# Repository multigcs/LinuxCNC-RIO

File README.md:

# LinuxCNC-RIO

please use: https://github.com/multigcs/riocore

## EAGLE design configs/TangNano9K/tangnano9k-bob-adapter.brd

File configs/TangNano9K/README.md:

# Tang Nano 9K with 5axis-BOB

https://wiki.sipeed.com/hardware/en/tang/Tang-Nano-9K/Nano-9K.html

Install: see INSTALL.md

## Known-Issues:
* openFPGAloader will not work on Raspberry Pi, you have to use another host to flash the FPGA !
* sometimes i have problems with the opensource toolchain and extended configurations, like encoder value will not change
* you can also using the gowin toolchain if you have problems with the opensource one, all required files are generated

### LinuxCNC-RIO mixed joint types (on TangNano9K - FPGA)
")

## BOB-Adapter SPI-Pins:

| BOB-Adapter | FUNC | FPGA-Pin |Raspberry-GPIO | Raspberry-Pin |
| --- | --- | --- | --- | --- |
| 1 | 5V |  |  | 2 |
| 2 | MOSI | 48 | GPIO10 (MOSI) | 19 |
| 3 | MISO |  49 |GPIO9 (MISO) | 21 |
| 4 | SCK |  31 |GPIO11 (SCLK) | 23 |
| 5 | CS |  32 |GPIO7 (CE1) | 26 |
| 6 | GND | | | 6 |

## BOB-Adapter Expansion-Pins:
| BOB-Adapter | FUNC | FPGA-Pin | 
| --- | --- | --- |
| 1 | OUT | 73 |
| 2 | IN | 72 |
| 3 | CLK | 71 |
| 4 | LOAD | 70 |
| 5 | 5V | |
| 6 | GND | |

## BOB-Adapter extra Input-Pins:
| BOB-Adapter | FUNC | FPGA-Pin |
| --- | --- | --- |
| 1 | 5V | |
| 2 | DIN5 | 79 |
| 3 | DIN6 | 80 |
| 4 | DIN7 | 81 |
| 5 | DIN8 | 82 |
| 6 | DIN9 | 83 |
| 7 | DIN10 | 84 |
| 8 | DIN11 | 85 |
| 9 | DIN12 | 86 |
| 10 | GND | |

## Mapping: 5Axis-BOB to FPGA 

| BOB5X | FUNC | FPGA-Pin |
| --- | --- | --- |
| P1 | PWM | 55 |
| P2 | STP_X | 54 |
| P3 | DIR_X | 53 |
| P4 | STP_Y | 51 |
| P5 | DIR_Y | 42 |
| P6 | STP_Z | 41 |
| P7 | DIR_Z | 35 |
| P8 | STP_A | 40 |
| P9 | DIR_A | 34 |
| P10 | DIN0 | 33 |
| P11 | DIN1 | 30 |
| P12 | DIN2 | 29 |
| P13 | DIN3 | 28 |
| P14 | EN | 69 |
| P15 | DIN4 | 68 |
| P16 | STP_B | 57 |
| P17 | DIR_B / Relais | 56 |

## Mapping: FPGA Onboard Components

| Component | FUNC | FPGA-Pin |
| --- | --- | --- |
| LED1 | BLINK | 10 |
| LED2 | ERROR | 11 |
| LED3 | DOUT1 | 13 |
| LED4 | DOUT2 | 14 |
| LED5 | DOUT3 | 15 |
| LED6 | DOUT4 | 16 |
| BTN_S1 | VIN1+ | 4 |
| BTN_S2 | VIN1- | 3 |

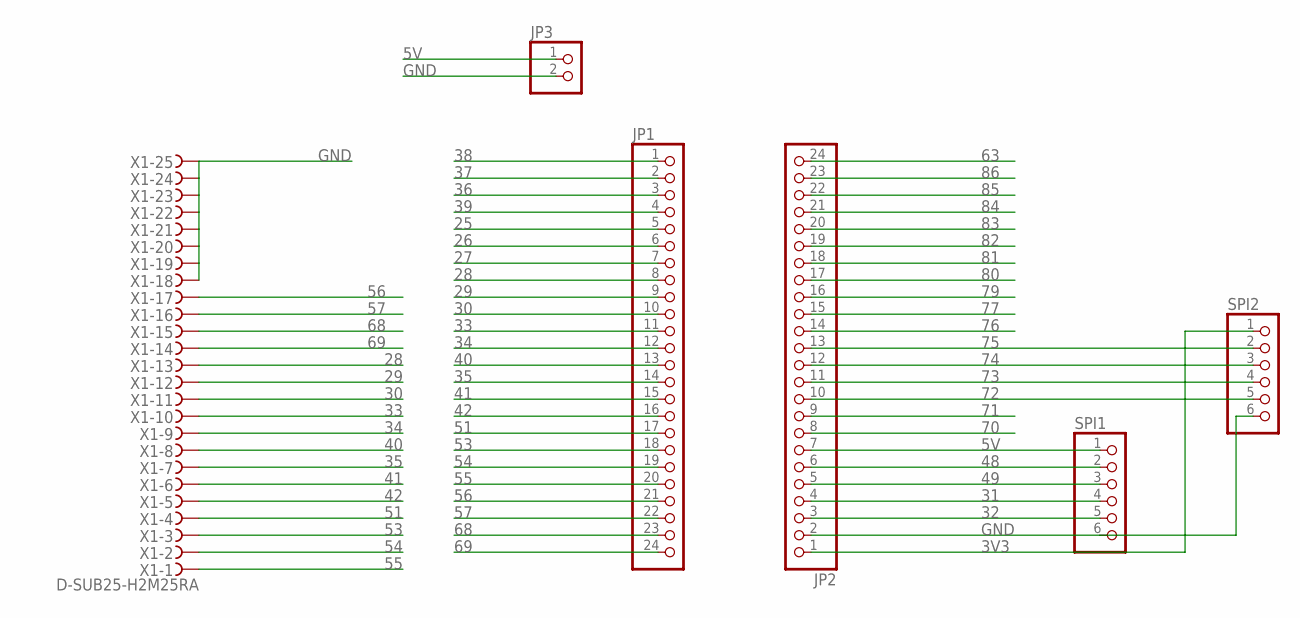
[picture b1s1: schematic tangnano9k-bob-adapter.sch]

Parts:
JP1, JP2: PINHD-1X24; 1X24
JP3: PINHD-1X2; 1X02
SPI1, SPI2: PINHD-1X6; 1X06
X1: D-SUB25-H2M25RA; H2M25RA

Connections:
3V3: JP2.1, SPI2.1
5V: JP2.7, JP3.1, SPI1.1
25: JP1.5
26: JP1.6
27: JP1.7
28: JP1.8, X1.13
29: JP1.9, X1.12
30: JP1.10, X1.11
31: JP2.4, SPI1.4
32: JP2.3, SPI1.5
33: JP1.11, X1.10
34: JP1.12, X1.9
35: JP1.14, X1.7
36: JP1.3
37: JP1.2
38: JP1.1
39: JP1.4
40: JP1.13, X1.8
41: JP1.15, X1.6
42: JP1.16, X1.5
48: JP2.6, SPI1.2
49: JP2.5, SPI1.3
51: JP1.17, X1.4
53: JP1.18, X1.3
54: JP1.19, X1.2
55: JP1.20, X1.1
56: JP1.21, X1.17
57: JP1.22, X1.16
63: JP2.24
68: JP1.23, X1.15
69: JP1.24, X1.14
70: JP2.8
71: JP2.9
72: JP2.10, SPI2.5
73: JP2.11, SPI2.4
74: JP2.12, SPI2.3
75: JP2.13, SPI2.2
76: JP2.14
77: JP2.15
79: JP2.16
80: JP2.17
81: JP2.18
82: JP2.19
83: JP2.20
84: JP2.21
85: JP2.22
86: JP2.23
GND: JP2.2, JP3.2, SPI1.6, SPI2.6, X1.18, X1.19, X1.20, X1.21, X1.22, X1.23, X1.24, X1.25

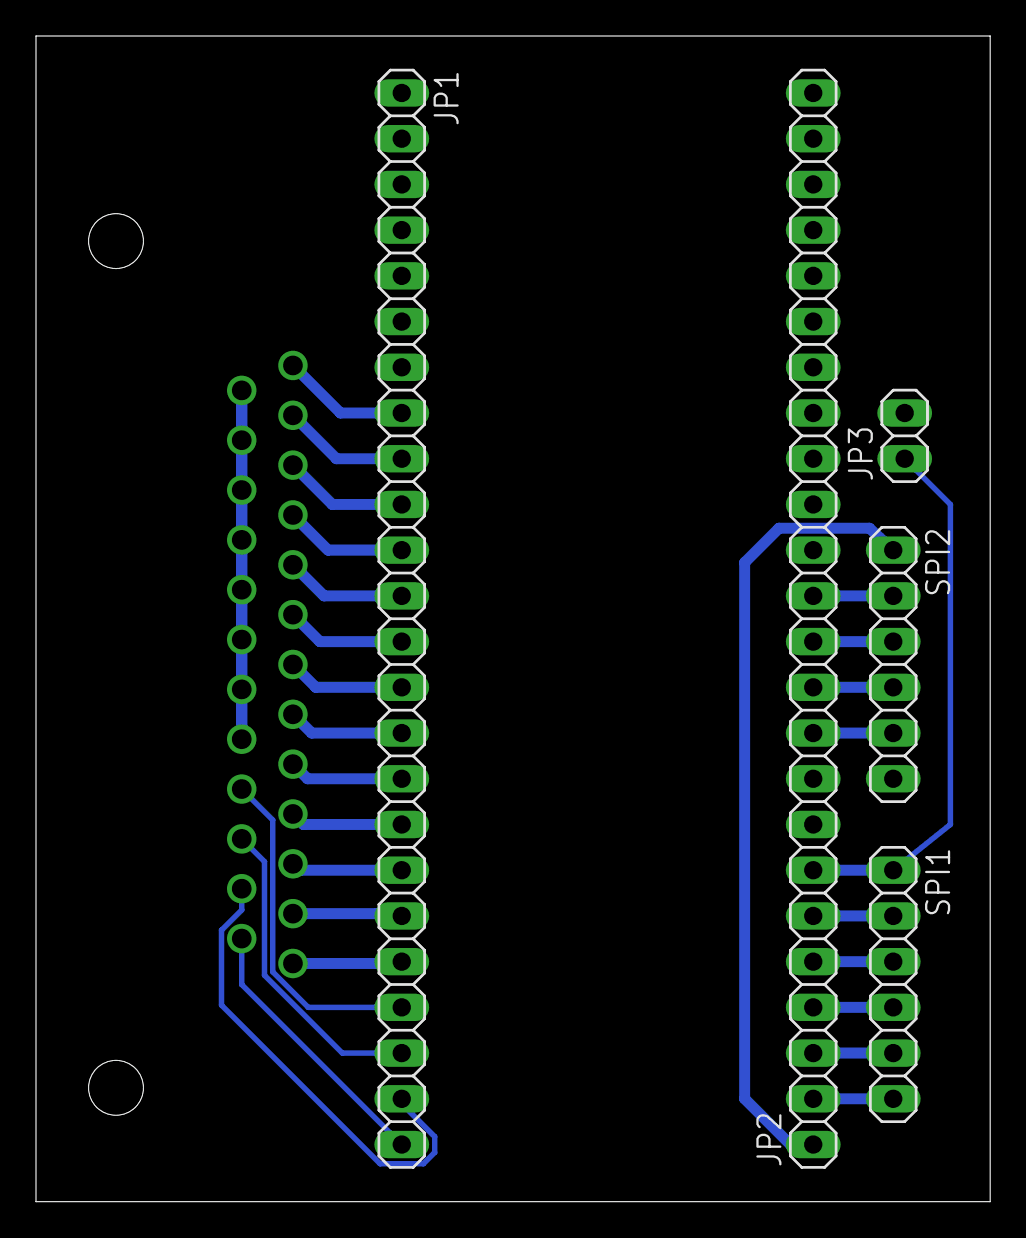
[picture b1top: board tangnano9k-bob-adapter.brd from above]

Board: 2 copper layers, 53.0 x 64.8 mm, 6 parts (1 on the bottom side), 28 nets.

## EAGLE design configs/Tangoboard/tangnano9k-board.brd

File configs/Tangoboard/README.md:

# Tango-Board for Tang Nano 9K

https://wiki.sipeed.com/hardware/en/tang/Tang-Nano-9K/Nano-9K.html

Install: see INSTALL.md

## Known-Issues:
* openFPGAloader will not work on Raspberry Pi, you have to use another host to flash the FPGA !
* sometimes i have problems with the opensource toolchain and extended configurations, like encoder value will not change
* you can also using the gowin toolchain if you have problems with the opensource one, all required files are generated

## BOM:

[Reichelt](https://www.reichelt.de/my/2063538)

## Pinout:

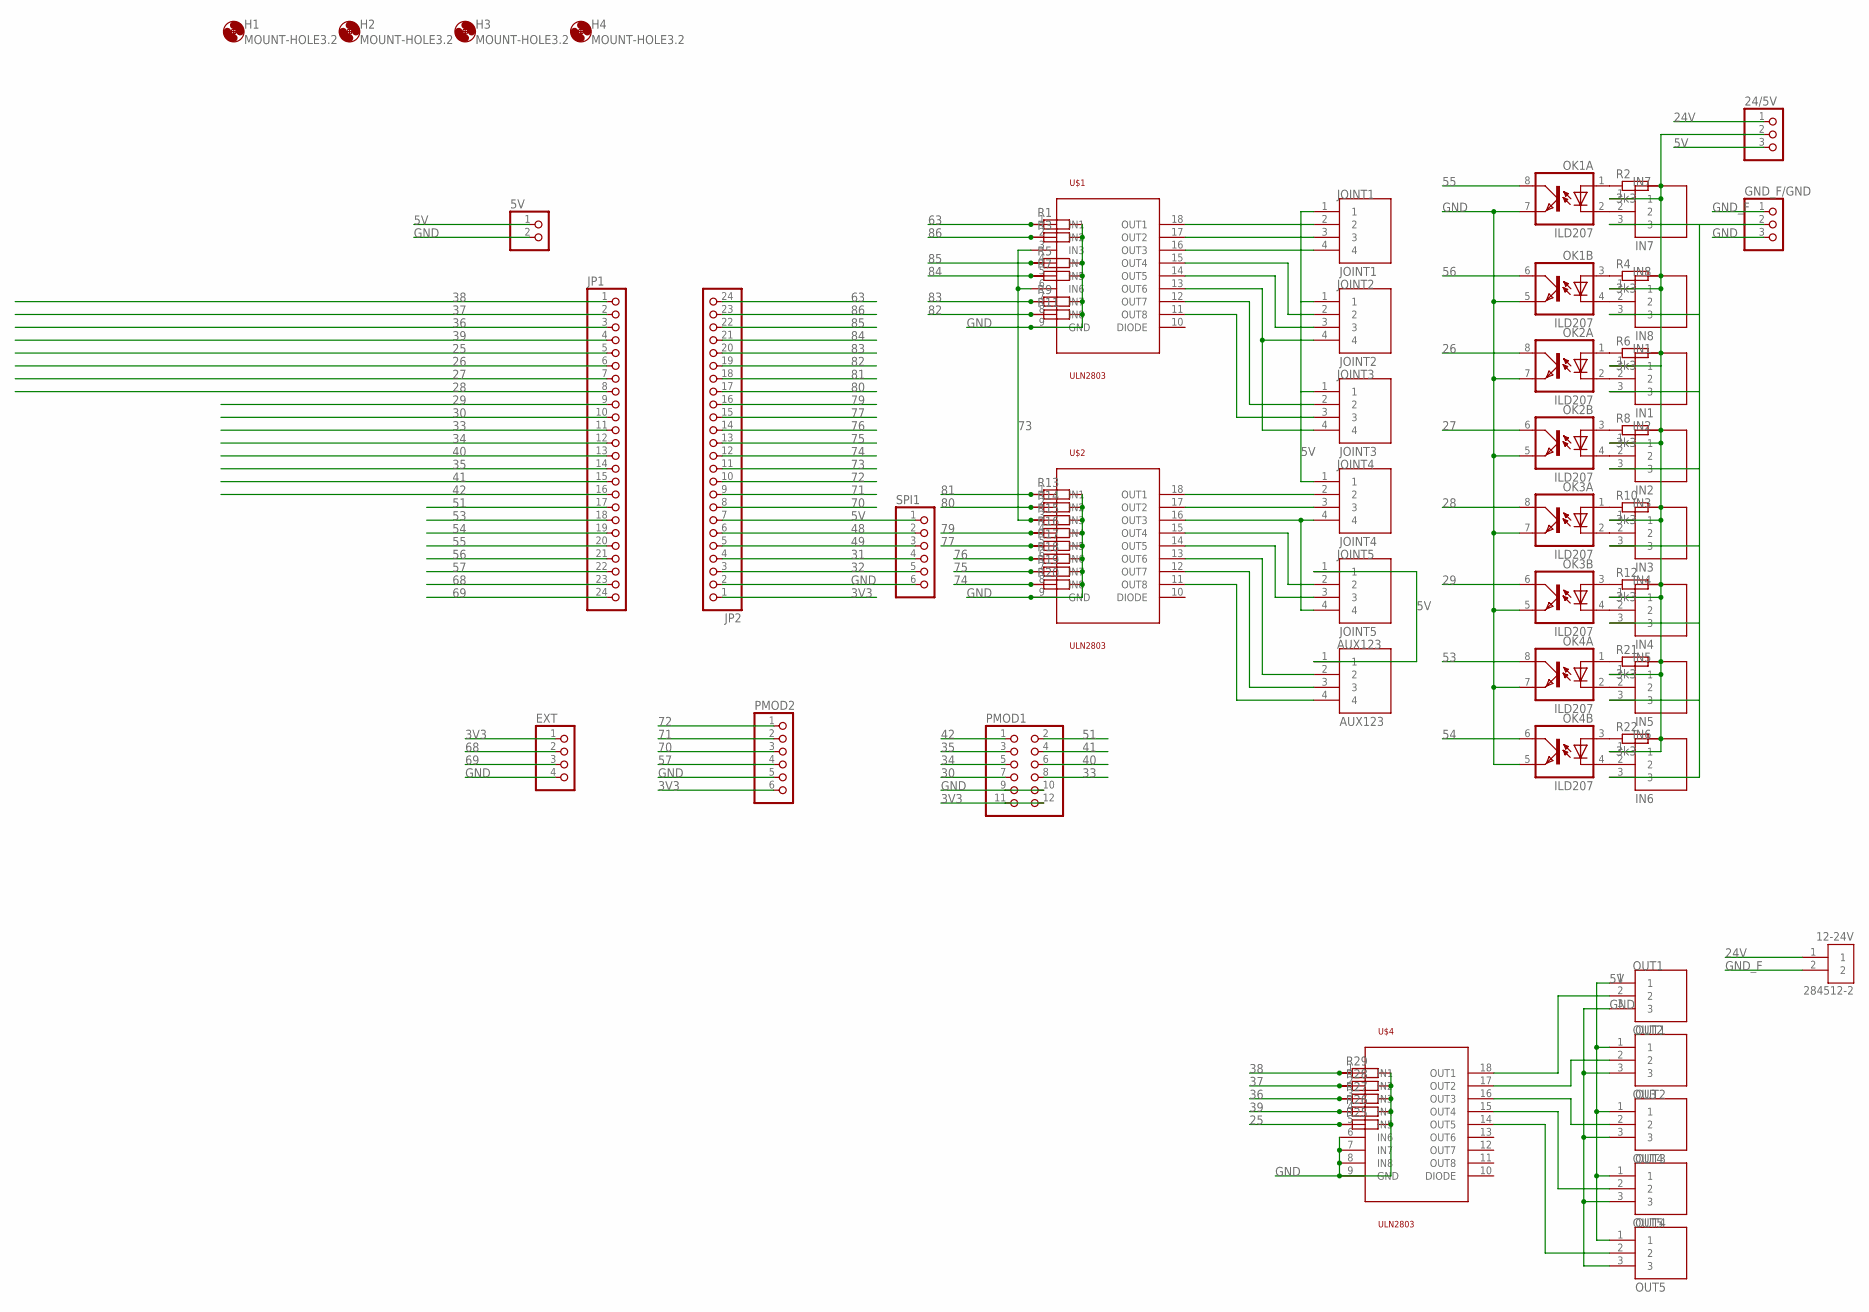
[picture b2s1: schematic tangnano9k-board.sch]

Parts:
5V: PINHD-1X2; 1X02
12-24V: 284512-2; TE_284512-2
24/5V: PINHD-1X3; 1X03
AUX123: AUX123; TE_284512-4
EXT: PINHD-1X4; 1X04
GND_F/GND: PINHD-1X3; 1X03
H1, H2, H3, H4: MOUNT-HOLE3.2; 3,2
IN1: IN1; TE_284512-3
IN2: IN2; TE_284512-3
IN3: IN3; TE_284512-3
IN4: IN4; TE_284512-3
IN5: IN5; TE_284512-3
IN6: IN6; TE_284512-3
IN7: IN7; TE_284512-3
IN8: IN8; TE_284512-3
JOINT1: JOINT1; TE_284512-4
JOINT2: JOINT2; TE_284512-4
JOINT3: JOINT3; TE_284512-4
JOINT4: JOINT4; TE_284512-4
JOINT5: JOINT5; TE_284512-4
JP1, JP2: PINHD-1X24; 1X24
OK1, OK2, OK3, OK4: ILD207; SOIC08
OU3: OUT3; TE_284512-3
OUT1: OUT1; TE_284512-3
OUT2: OUT2; TE_284512-3
OUT4: OUT4; TE_284512-3
OUT5: OUT5; TE_284512-3
PMOD1: PINHD-2X6; 2X06
PMOD2: PINHD-1X6; 1X06
R1, R3, R5, R7, R9, R11, R13, R14, R15, R16, R17, R18, R19, R20, R25, R26, R27, R28, R29: R-EU_M0805; M0805
R2, R4, R6, R8, R10, R12, R21, R22: 3k3; M0805
SPI1: PINHD-1X6; 1X06
U$1, U$2, U$4: ULN2803; SO18L

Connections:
3V3: EXT.1, JP2.1, PMOD1.11, PMOD1.12, PMOD2.6
5V: 5V.1, 24/5V.3, AUX123.1, JOINT1.1, JOINT2.1, JOINT3.1, JOINT4.1, JOINT5.1, JP2.7, OU3.1, OUT1.1, OUT2.1, OUT4.1, OUT5.1, SPI1.1
24V: 12-24V.1, 24/5V.1
25: JP1.5, R25.1, U$4.5 (IN5)
26: JP1.6, OK2.8 (COL)
27: JP1.7, OK2.6 (COL)
28: JP1.8, OK3.8 (COL)
29: JP1.9, OK3.6 (COL)
30: JP1.10, PMOD1.7
31: JP2.4, SPI1.4
32: JP2.3, SPI1.5
33: JP1.11, PMOD1.8
34: JP1.12, PMOD1.5
35: JP1.14, PMOD1.3
36: JP1.3, R27.1, U$4.3 (IN3)
37: JP1.2, R28.1, U$4.2 (IN2)
38: JP1.1, R29.1, U$4.1 (IN1)
39: JP1.4, R26.1, U$4.4 (IN4)
40: JP1.13, PMOD1.6
41: JP1.15, PMOD1.4
42: JP1.16, PMOD1.1
48: JP2.6, SPI1.2
49: JP2.5, SPI1.3
51: JP1.17, PMOD1.2
53: JP1.18, OK4.8 (COL)
54: JP1.19, OK4.6 (COL)
55: JP1.20, OK1.8 (COL)
56: JP1.21, OK1.6 (COL)
57: JP1.22, PMOD2.4
63: JP2.24, R1.1, U$1.1 (IN1)
68: EXT.2, JP1.23
69: EXT.3, JP1.24
70: JP2.8, PMOD2.3
71: JP2.9, PMOD2.2
72: JP2.10, PMOD2.1
73: JP2.11, R15.1, U$1.3 (IN3), U$1.6 (IN6), U$2.3 (IN3)
74: JP2.12, R20.1, U$2.8 (IN8)
75: JP2.13, R19.1, U$2.7 (IN7)
76: JP2.14, R18.1, U$2.6 (IN6)
77: JP2.15, R17.1, U$2.5 (IN5)
79: JP2.16, R16.1, U$2.4 (IN4)
80: JP2.17, R14.1, U$2.2 (IN2)
81: JP2.18, R13.1, U$2.1 (IN1)
82: JP2.19, R11.1, U$1.8 (IN8)
83: JP2.20, R9.1, U$1.7 (IN7)
84: JP2.21, R7.1, U$1.5 (IN5)
85: JP2.22, R5.1, U$1.4 (IN4)
86: JP2.23, R3.1, U$1.2 (IN2)
GND: 5V.2, EXT.4, GND_F/GND.3, JP2.2, OK1.5 (EMIT), OK1.7 (EMIT), OK2.5 (EMIT), OK2.7 (EMIT), OK3.5 (EMIT), OK3.7 (EMIT), OK4.5 (EMIT), OK4.7 (EMIT), OU3.3, OUT1.3, OUT2.3, OUT4.3, OUT5.3, PMOD1.9, PMOD1.10, PMOD2.5, R1.2, R3.2, R5.2, R7.2, R9.2, R11.2, R13.2, R14.2, R15.2, R16.2, R17.2, R18.2, R19.2, R20.2, R25.2, R26.2, R27.2, R28.2, R29.2, SPI1.6, U$1.9 (GND), U$2.9 (GND), U$4.6 (IN6), U$4.7 (IN7), U$4.8 (IN8), U$4.9 (GND)
GND_F: 12-24V.2, GND_F/GND.1
unnamed: JOINT1.4, U$1.16 (OUT3)
unnamed: JOINT1.3, U$1.17 (OUT2)
unnamed: JOINT1.2, U$1.18 (OUT1)
unnamed: JOINT2.2, U$1.15 (OUT4)
unnamed: JOINT2.3, U$1.14 (OUT5)
unnamed: JOINT2.4, JOINT3.4, U$1.13 (OUT6)
unnamed: JOINT3.2, U$1.12 (OUT7)
unnamed: JOINT3.3, U$1.11 (OUT8)
unnamed: JOINT4.2, U$2.18 (OUT1)
unnamed: JOINT4.3, U$2.17 (OUT2)
unnamed: JOINT4.4, JOINT5.4, U$2.16 (OUT3)
unnamed: JOINT5.2, U$2.15 (OUT4)
unnamed: JOINT5.3, U$2.14 (OUT5)
unnamed: AUX123.2, U$2.13 (OUT6)
unnamed: AUX123.3, U$2.12 (OUT7)
unnamed: AUX123.4, U$2.11 (OUT8)
unnamed: IN7.2, OK1.2 (C)
unnamed: IN8.2, OK1.4 (C)
unnamed: IN1.2, OK2.2 (C)
unnamed: IN2.2, OK2.4 (C)
unnamed: IN3.2, OK3.2 (C)
unnamed: IN4.2, OK3.4 (C)
unnamed: IN5.2, OK4.2 (C)
unnamed: IN6.2, OK4.4 (C)
unnamed: OK1.1 (A), R2.1
unnamed: OK1.3 (A), R4.1
unnamed: OK2.1 (A), R6.1
unnamed: OK2.3 (A), R8.1
unnamed: OK3.1 (A), R10.1
unnamed: OK3.3 (A), R12.1
unnamed: OK4.1 (A), R21.1
unnamed: OK4.3 (A), R22.1
unnamed: OUT2.2, U$4.17 (OUT2)
unnamed: OU3.2, U$4.16 (OUT3)
unnamed: OUT4.2, U$4.15 (OUT4)
unnamed: OUT5.2, U$4.14 (OUT5)
unnamed: OUT1.2, U$4.18 (OUT1)
unnamed: 24/5V.2, IN1.1, IN2.1, IN3.1, IN4.1, IN5.1, IN6.1, IN7.1, IN8.1, R2.2, R4.2, R6.2, R8.2, R10.2, R12.2, R21.2, R22.2
unnamed: GND_F/GND.2, IN1.3, IN2.3, IN3.3, IN4.3, IN5.3, IN6.3, IN7.3, IN8.3

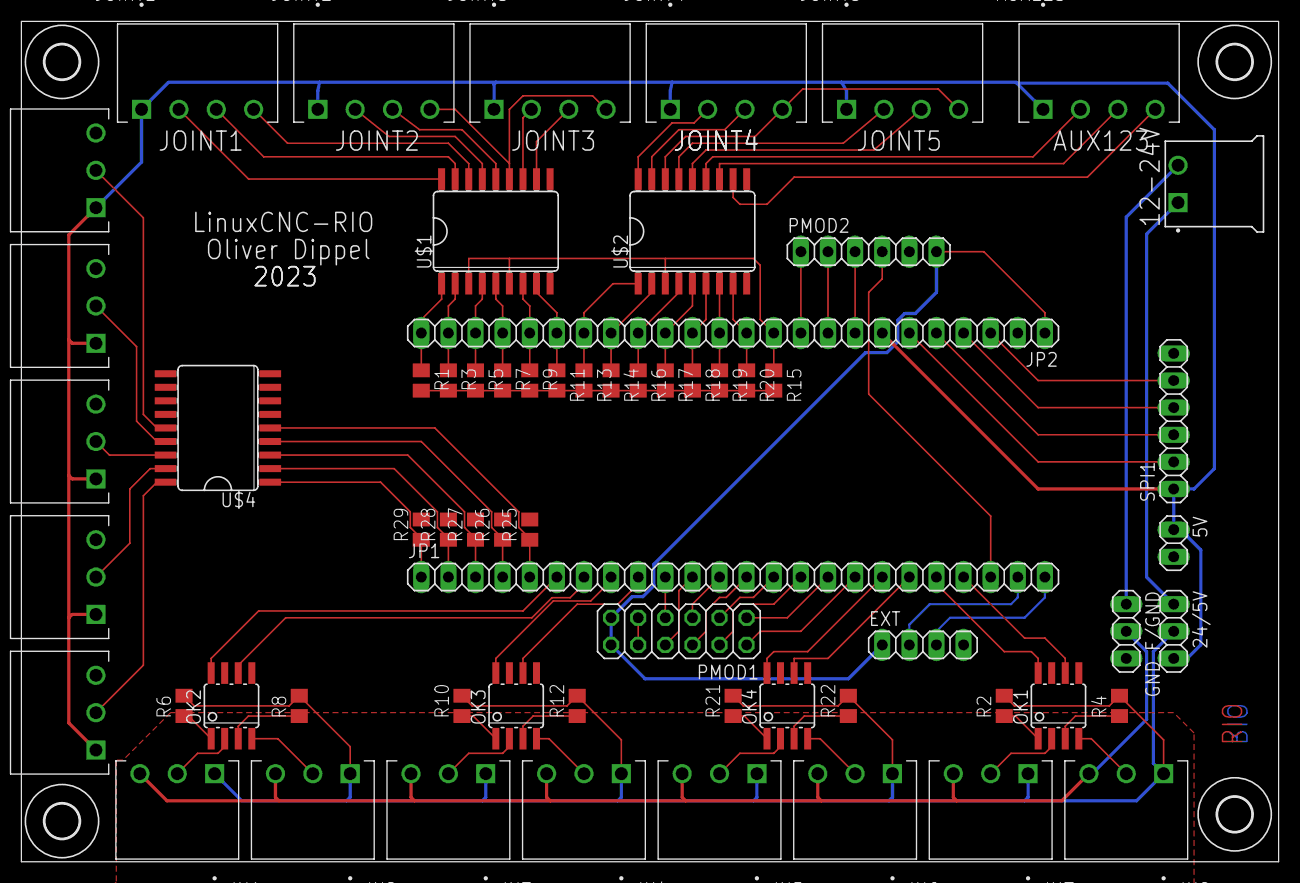
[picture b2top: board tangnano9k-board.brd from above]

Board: 2 copper layers, 117.8 x 78.7 mm, 67 parts (0 on the bottom side), 89 nets.

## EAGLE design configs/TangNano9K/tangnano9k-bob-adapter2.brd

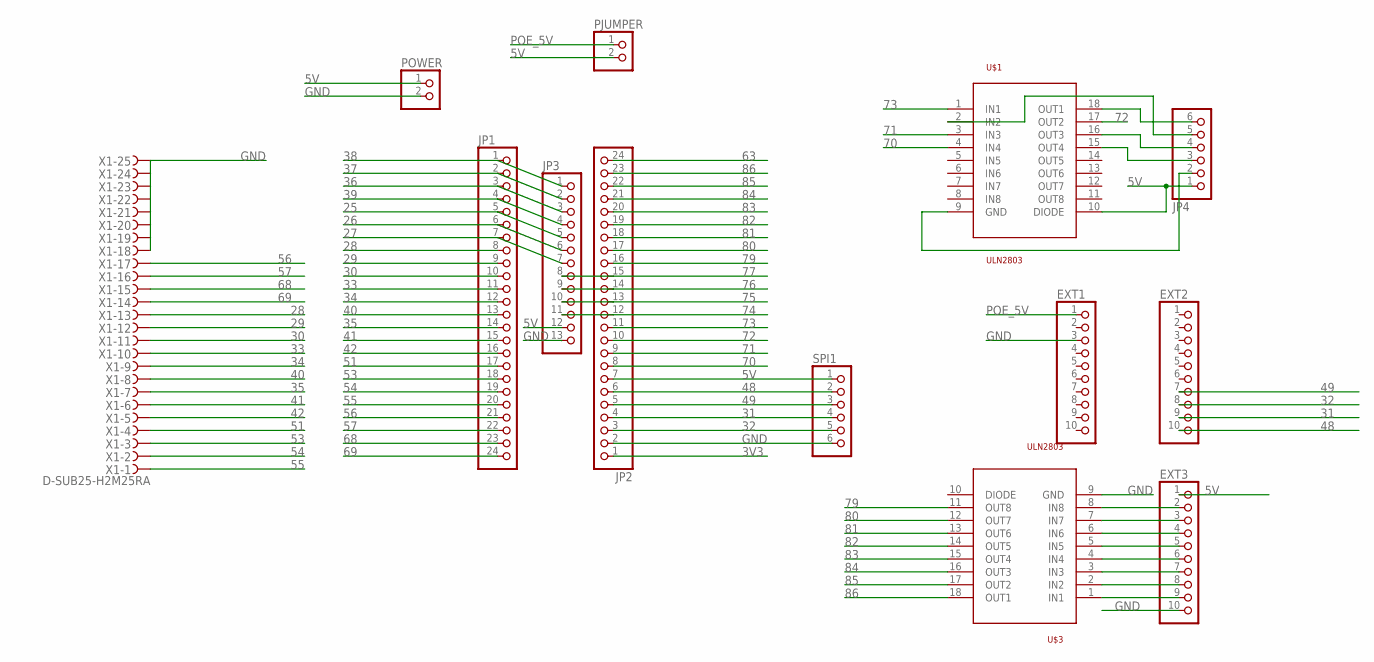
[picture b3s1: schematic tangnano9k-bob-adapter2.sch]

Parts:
EXT1, EXT2, EXT3: PINHD-1X10; 1X10
JP1, JP2: PINHD-1X24; 1X24
JP3: PINHD-1X13; 1X13
JP4: PINHD-1X6/90; 1X06/90
PJUMPER: PINHD-1X2; 1X02
POWER: PINHD-1X2; 1X02
SPI1: PINHD-1X6; 1X06
U$1, U$3: ULN2803; SO18L
X1: D-SUB25-H2M25RA; H2M25RA

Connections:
3V3: JP2.1
5V: EXT3.1, JP2.7, JP3.12, JP4.1, PJUMPER.2, POWER.1, SPI1.1, U$1.10 (DIODE)
25: JP1.5, JP3.5
26: JP1.6, JP3.6
27: JP1.7, JP3.7
28: JP1.8, X1.13
29: JP1.9, X1.12
30: JP1.10, X1.11
31: EXT2.9, JP2.4, SPI1.4
32: EXT2.8, JP2.3, SPI1.5
33: JP1.11, X1.10
34: JP1.12, X1.9
35: JP1.14, X1.7
36: JP1.3, JP3.3
37: JP1.2, JP3.2
38: JP1.1, JP3.1
39: JP1.4, JP3.4
40: JP1.13, X1.8
41: JP1.15, X1.6
42: JP1.16, X1.5
48: EXT2.10, JP2.6, SPI1.2
49: EXT2.7, JP2.5, SPI1.3
51: JP1.17, X1.4
53: JP1.18, X1.3
54: JP1.19, X1.2
55: JP1.20, X1.1
56: JP1.21, X1.17
57: JP1.22, X1.16
63: JP2.24
68: JP1.23, X1.15
69: JP1.24, X1.14
70: JP2.8, U$1.4 (IN4)
71: JP2.9, U$1.3 (IN3)
72: JP2.10, U$1.17 (OUT2)
73: JP2.11, U$1.1 (IN1)
74: JP2.12, JP3.11
75: JP2.13, JP3.10
76: JP2.14, JP3.9
77: JP2.15, JP3.8
79: JP2.16, U$3.11 (OUT8)
80: JP2.17, U$3.12 (OUT7)
81: JP2.18, U$3.13 (OUT6)
82: JP2.19, U$3.14 (OUT5)
83: JP2.20, U$3.15 (OUT4)
84: JP2.21, U$3.16 (OUT3)
85: JP2.22, U$3.17 (OUT2)
86: JP2.23, U$3.18 (OUT1)
GND: EXT1.3, EXT3.10, JP2.2, JP3.13, JP4.2, POWER.2, SPI1.6, U$1.9 (GND), U$3.9 (GND), X1.18, X1.19, X1.20, X1.21, X1.22, X1.23, X1.24, X1.25
unnamed: EXT3.9, U$3.1 (IN1)
unnamed: JP4.6, U$1.18 (OUT1)
unnamed: JP4.5, U$1.2 (IN2)
unnamed: JP4.4, U$1.16 (OUT3)
unnamed: JP4.3, U$1.15 (OUT4)
unnamed: EXT3.8, U$3.2 (IN2)
unnamed: EXT3.7, U$3.3 (IN3)
unnamed: EXT3.6, U$3.4 (IN4)
unnamed: EXT3.5, U$3.5 (IN5)
unnamed: EXT3.4, U$3.6 (IN6)
unnamed: EXT3.3, U$3.7 (IN7)
unnamed: EXT3.2, U$3.8 (IN8)
POE_5V: EXT1.1, PJUMPER.1

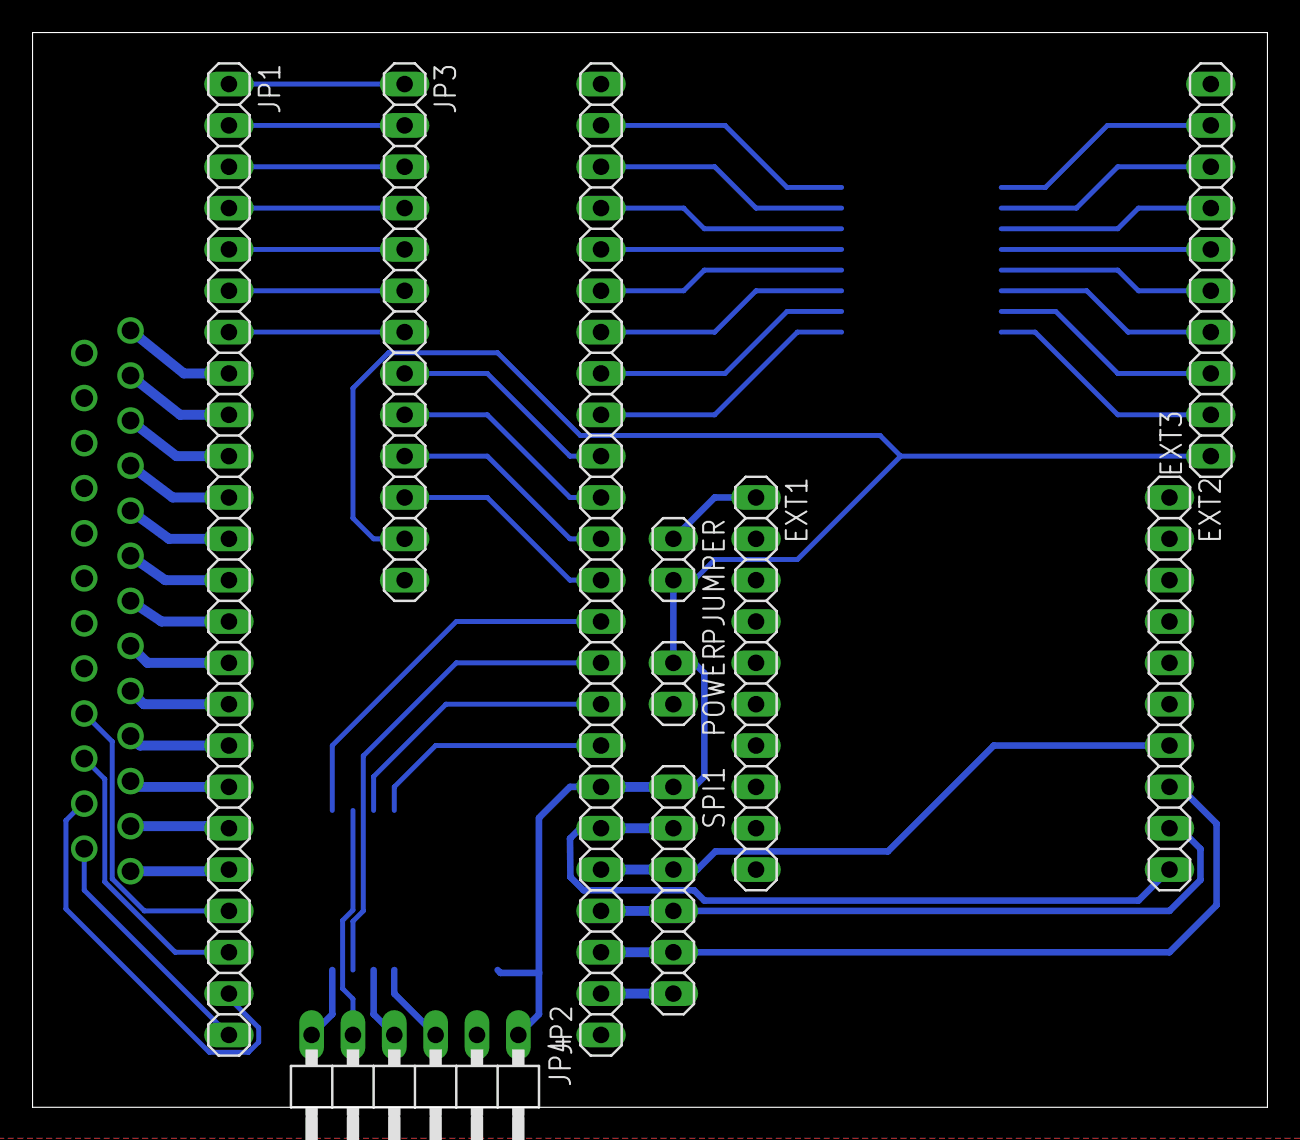
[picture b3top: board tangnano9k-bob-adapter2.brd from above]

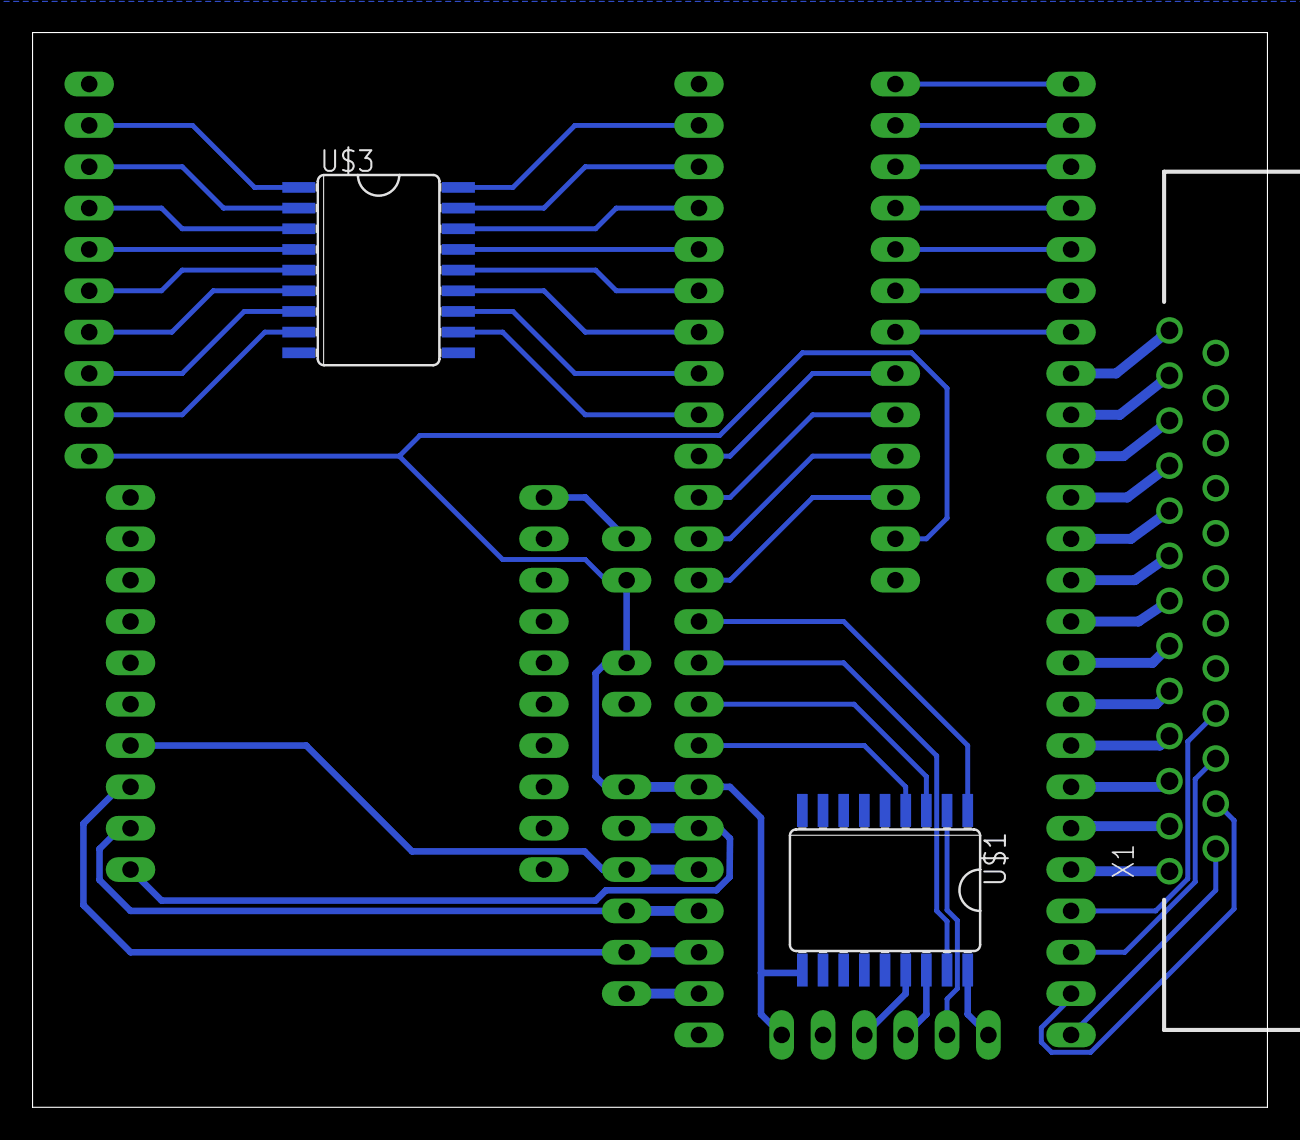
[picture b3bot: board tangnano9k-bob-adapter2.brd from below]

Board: 2 copper layers, 75.9 x 66.0 mm, 13 parts (3 on the bottom side), 59 nets.

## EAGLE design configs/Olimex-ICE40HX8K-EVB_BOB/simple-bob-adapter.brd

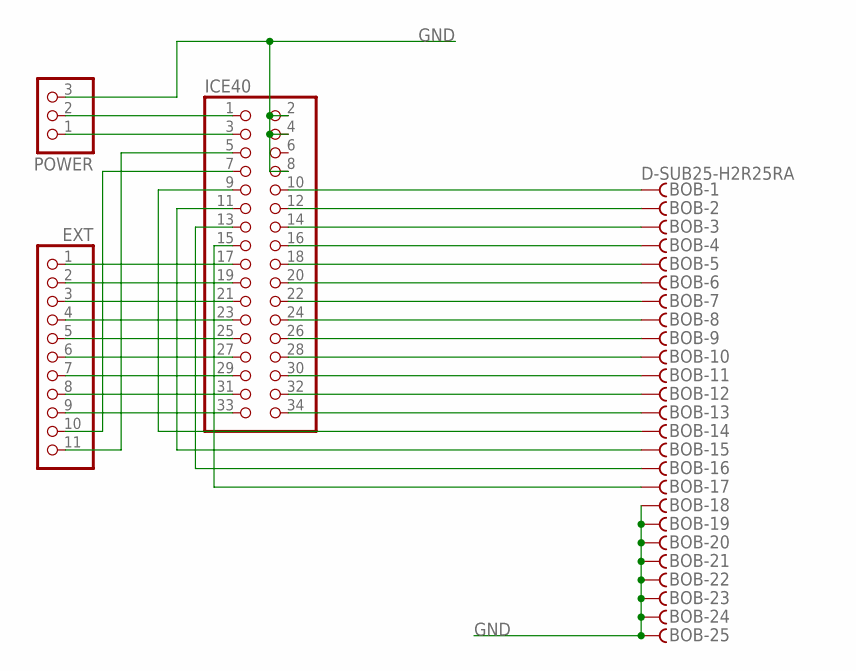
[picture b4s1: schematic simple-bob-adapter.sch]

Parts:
BOB: D-SUB25-H2R25RA; H2R25RA
EXT: PINHD-1X11; 1X11
ICE40: PINHD-2X17/90; 2X17/90
POWER: PINHD-1X3; 1X03

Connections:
GND: BOB.18, BOB.19, BOB.20, BOB.21, BOB.22, BOB.23, BOB.24, BOB.25, ICE40.2, ICE40.4, ICE40.8, POWER.3
unnamed: BOB.1, ICE40.10
unnamed: BOB.2, ICE40.12
unnamed: BOB.3, ICE40.14
unnamed: BOB.4, ICE40.16
unnamed: BOB.5, ICE40.18
unnamed: BOB.6, ICE40.20
unnamed: BOB.7, ICE40.22
unnamed: BOB.8, ICE40.24
unnamed: BOB.9, ICE40.26
unnamed: BOB.10, ICE40.28
unnamed: BOB.11, ICE40.30
unnamed: BOB.12, ICE40.32
unnamed: BOB.13, ICE40.34
unnamed: BOB.15, ICE40.11
unnamed: ICE40.3, POWER.1
unnamed: BOB.16, ICE40.13
unnamed: BOB.17, ICE40.15
unnamed: EXT.1, ICE40.17
unnamed: EXT.2, ICE40.19
unnamed: EXT.3, ICE40.21
unnamed: EXT.4, ICE40.23
unnamed: EXT.5, ICE40.25
unnamed: EXT.6, ICE40.27
unnamed: EXT.7, ICE40.29
unnamed: EXT.8, ICE40.31
unnamed: EXT.9, ICE40.33
unnamed: BOB.14, ICE40.9
unnamed: ICE40.1, POWER.2
unnamed: EXT.10, ICE40.7
unnamed: EXT.11, ICE40.5

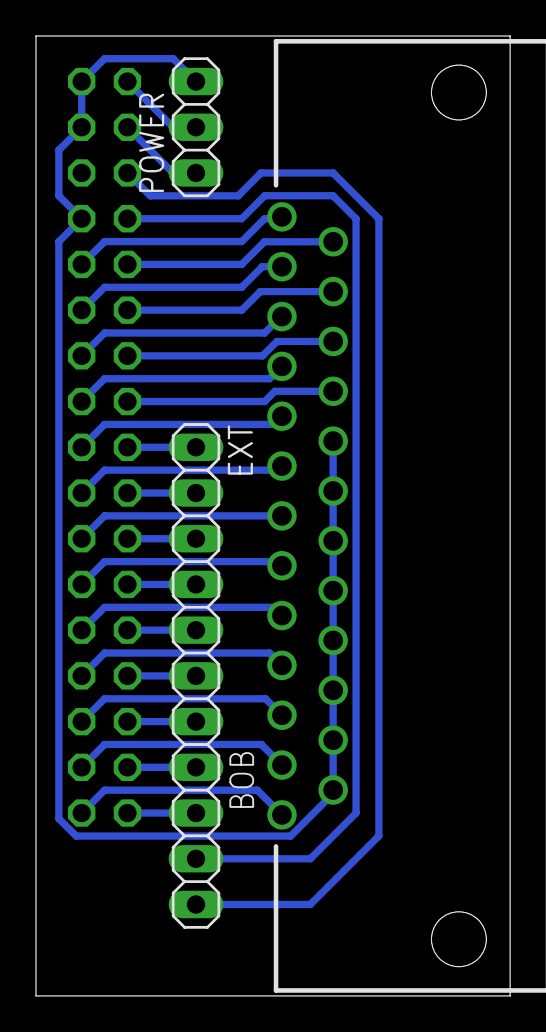
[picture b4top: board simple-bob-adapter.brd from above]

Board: 2 copper layers, 26.3 x 53.3 mm, 4 parts (1 on the bottom side), 31 nets.

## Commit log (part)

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2023-07-25 adding generate all option
2023-07-26 remove unused and duplicated code
2023-07-26 add link to Alhambra board
2023-07-27 update pinout / tangoboard
2023-07-28 initial support for TangNano20K / gowin ide only
2023-07-28 adding digitaljs files to gitignore
2023-07-28 testing svg in readme
2023-07-28 generate graphiz flowchart for each plugin
2023-07-28 readme
2023-07-30 adding connect info
2023-07-31 removing empty plugin
2023-07-31 reset config
2023-08-01 smale fixes
2023-08-01 addning TangNano20K sample config / thanks to TurBoss
2023-08-01 using dict for multiple pins / update qtsetup
2023-08-04 qtsetup.py - small fixes
2023-08-04 adding board images to setup gui
2023-08-04 preview generated files in qtsetup
2023-08-04 initial untested ds18b20 onewire support
2023-08-04 removing bad plugin: vin_ds18b20 / print only
2023-08-05 rewrite signal handling
2023-08-06 rewrite plugin structure / update configs / add config converter
2023-08-06 smalle changes
2023-08-06 small changes
2023-08-06 adding debounce to vin_frequency
2023-08-07 changing pin format for vout_pwm
2023-08-08 FIX: initialize ethernet before checking hardware
2023-08-08 Fix initialization order call Ethernet.Init() in first place
2023-08-08 fix use the correct ESP32 model for WROOM32
2023-08-08 adding options to setup vin pyvcp widgets
2023-08-11 adding NTC calc for ads1115 plugin
2023-08-11 adding NTC example
2023-08-11 adding example for water-flow-sensors
2023-08-11 smaller extra gui elements
2023-08-11 sort extra gui into tabs
2023-08-11 splitting config generator into def's
2023-08-14 fixing config generator
2023-08-14 initial qtdragon gui generator
2023-08-14 adding qtdragon gui template
2023-08-14 loading hal_manualtoolchange
2023-08-14 better ads setup / first offset then scale in rio.c
2023-08-14 fixing ads plugin
2023-08-15 adding hallabels to qtdragon generator (thanks to cmorley)
2023-08-15 better qtdragon gui widgets
2023-08-15 connecting more pins to qtdragon
2023-08-16 adding RIO page link
2023-08-16 updating readme
2023-08-16 better qtdragon gen
2023-08-16 adding din_toggle plugin
2023-08-17 adding wcomp test
2023-08-18 fixing hal generation for spindle plugin with feedback
2023-08-19 better gui generation
2023-08-19 adding vfdbridge
2023-08-21 adding input mixer
2023-08-22 fixing debounce (non-inverted) / bigger LED / adding debounce to din_bit
2023-08-22 allow int to setup debounce delay
2023-08-23 better error handling while loading json file
2023-08-23 adding some homing options to json
2023-08-23 adding axis names to json / allow multiple joints per axis
2023-08-23 workaround
2023-08-24 fixing multiple joints per axis
2023-08-24 fixing debounce
2023-08-24 adding hole_center.ngc for testing
2023-09-06 removing udp part from readme
2023-09-08 adding plug image
2023-09-08 adding standard connector definitions
2023-09-11 adding experimental Arty-a7-35t support
2023-09-11 update arty
2023-09-12 reformat firmware.py / split code into some functions
2023-09-12 cleaner rio.v generation
2023-09-12 fixing lpf pins / split toolchan builder
2023-09-12 cleanup .ini generator
2023-09-13 adding missing files
2023-09-14 simple z_touch.ngc
2023-09-14 supporting linuxcnc PID loop without encoder on stepper joints (set cl to true in json)
2023-09-14 fixing some qtdragon generator issues
2023-09-16 adding pullup support to vivado generator
2023-09-16 using openFPGALoader for arty board
2023-09-16 fixing serial in component generator
2023-09-16 better serial support in hal driver
2023-09-16 better serial support in test tool
2023-09-16 check interface type in spi plugin
2023-09-16 adding experimental uart interface plugin - will not work in linuxcnc
2023-09-18 fixing argparse
2023-09-18 adding projectLoader
2023-09-18 adding non generated qt-testgui.py to replace the qt_spitest.py tool
2023-09-18 adding simple generator test
2023-09-18 fixing tests
2023-09-18 fixing some warnings
2023-09-18 ignore warning in interface_uart.v
2023-09-18 plugin reader in loop
2023-09-19 fixing config generator - thanks to kzali
2023-09-19 fixing ip copy in interface plugin's
2023-09-20 moving uart.v into generator
2023-09-20 splitting uart.v in file per module / better verilator check
2023-09-21 using SCALE as float
2023-09-21 fixing test / adding testall.sh to generate bitfiles for all configs
2023-09-21 initial modbus/vfd support without extra mcu
2023-09-22 adding simple tool to calculate the debounce delay
2023-09-22 Fix joint_pwmdir enable signal wiring
2023-09-22 joint_pwmdir: fixing testbench
2023-09-22 quickfix: qtgui -> joint_pwmdir
2023-09-22 showing spindle feedback
2023-09-24 tests with picosoc
2023-09-24 adding gtkw file for pwmdir testbench
2023-09-24 fixing qt-testgui.py
2023-09-24 adding module loader
2023-09-24 fixing rio.v without enables
2023-09-24 fix primer20k
2023-09-24 adding paramerts
2023-09-24 TangPrimer20K - testing modules
2023-09-25 show connection status in new test-gui
2023-09-27 tang*20K now supported in yosys / adding support for system-verilog with gowin
2023-09-27 fixing family for TangPrimer20K
2023-09-27 fixing family for TangPrimer20K - in nextpnr-gowin it's GW2A-18 - in gowin it's GW2A-18C - grrrrrr
2023-09-27 update config
2023-09-27 update module
2023-09-27 removing debug line
2023-09-29 new experimental plugin: interface_udp_tangprimer20k
2023-09-29 setting top module for gowin
2023-09-29 converting system-verilog modules to verilog
2023-09-29 adding udp watchdog / checking message id
2023-09-29 init socket at startup
2023-09-29 set sourceport to 2390 to allow comunication with linuxcnc
2023-10-02 moving pll out of the interface module
2023-10-05 fixing board name - tanks to TurBoss
2023-10-10 new module based setup for the arty board
2023-10-15 fixing makefile
2023-10-17 fixing jcon
2023-10-19 tests with icebreaker
2023-10-19 experimental component modbus comunication
2023-10-23 adding signal infos
2023-10-24 adding graphviz output for testing
2023-10-26 adding missing file
2023-10-26 updating files
2023-10-26 adding firmware files for picorv32
2023-10-26 test
2023-10-26 working with icebreaker
2023-10-27 tests with arty board - problem with flash start >= 1M
2023-10-27 some little updates from picosoc branch
2023-10-27 adding support for non quad flash (spi only)
2023-10-27 works on arty and icebreaker
2023-10-27 support multiple peripheral modules
2023-10-27 move peripheral into single files
2023-10-27 auto generate peripheral.v and registers.h
2023-10-28 no need to define interfaces or other plugins, softcore only
2023-10-29 move peripherals into rio.v / enable some calculation features
2023-10-30 update configs
2023-10-30 defaults
2023-10-30 fixing arty soc build
2023-10-30 fixing ice40 build / dsp flag
2023-10-30 picosoc runs on ecp5 / supporting USRMCLK pin def
2023-10-31 fixing pins
2023-10-31 adding initial support for quartus toolchain
2023-10-31 testing verilog parser
2023-10-31 update parser
2023-10-31 fixing quartus generator
2023-10-31 adding pullup support to quartus
2023-10-31 rename pins file
2023-11-01 better parser / docgen
2023-11-01 flow charts
2023-11-02 hdmi text-output
2023-11-03 more args
2023-11-03 syntax highlighting
2023-11-03 moving doc-tool into generator
2023-11-03 fixing encoder as jogwheel
2023-11-03 adding initial build support for ise toolchain
2023-11-03 better diamont support with makefile
2023-11-03 adding missing hdmi files
2023-11-03 removing debug lines
2023-11-03 some fixes / readme
2023-11-04 some fixes
2023-11-04 adding simple 7seg plugin
2023-11-04 adding simple IR plugin
2023-11-04 adding simple ADC plugin (tlc549c)
2023-11-04 adding simple ws2812b plugin (vout + 3xdout)
2023-11-06 some small fixes
2023-11-06 adding test config for EP4CE6E22C8 and xc3s250e
2023-11-06 adding test config for bugblat_pif2
2023-11-06 fixing clock
2023-11-06 update from main
2023-11-06 better makefile for the vivado toolchain
2023-11-06 ganerate better makefiles
2023-11-07 adding some infos to rio.v
2023-11-08 show signals in flow chart
2023-11-08 show all signals in flow chart
2023-11-09 renaming config folders (board-name)
2023-11-09 reformat json / set name in json to directory name
2023-11-09 rename firmware to gateware
2023-11-09 adding minimal config for each board
2023-11-09 update doc generator
2023-11-09 removing old configs
2023-11-09 adding main configs
2023-11-09 moving pisosoc configs in extra file
2023-11-09 fixing picosoc firmware generation
2023-11-18 fix makefiles for tang primer 20k
2023-11-19 adding verilator target for testing
2023-11-20 fixing hy_vfd config generator
2023-11-24 fixing diamond build
2023-11-24 fixing diamond OSCH
2023-11-28 fixing MIN_LIMIT/MAX_LIMIT
2023-12-01 fixing double verilog files
2023-12-01 add reset buttons to test-tool some fixes
2023-12-01 setup hal signals
2023-12-01 adding fwd/rev/stop and speed commands
2023-12-01 cleanup and hycomm_ok status
2023-12-01 adding hal/ini config
2023-12-01 using right calculations and feedback
2023-12-01 adding readme
2023-12-05 adding toolchain comment to makefile
2023-12-06 initial config for Altera10M08Eval
2023-12-07 adding interfaces to max10 board / add info to spi-test title
2023-12-08 adding simple quartus pll helper script
2023-12-10 adding pcf8574 support
2023-12-10 fixing vout_rcservo plugin
2023-12-10 adding ds18b20 1wire support
2023-12-10 adding ds18b20 1wire and ps2 keyboard support
2023-12-11 removing untested modbus stuff
2023-12-11 add support for dio/aio setup / update readme
2023-12-12 reformating python files
2023-12-12 reformating python files using isort and black
2023-12-12 fixing some flake8 warnings
2023-12-12 fixed SPI bus hang when linuxcnc crashes and removed hard coded SPI pins
2023-12-12 updated generator with untested heredocs, no idea if that works
2023-12-12 fixing readme
2023-12-12 simplify config
2023-12-12 adding rpi spi setup to config
2023-12-12 cleanup / add rpi pin setup to generator
2023-12-12 adding notice to rio.c
2023-12-12 adding unipolar-stepper plugin
2023-12-16 adding wiznet w5500 interface
2023-12-16 adding timout to w5500 interface / checking rx header
2023-12-16 small updates
2023-12-16 better debug
2023-12-16 better error handling in w5500 and rio.c
2023-12-16 mac in setup / reformat / msgid check
2023-12-16 fixing some warings
2023-12-17 setup RX buffer size
2023-12-17 small fix
2023-12-17 adding max6675 plugin / Thermocouple-Sensor
2023-12-17 adding support for multiple ws2812's
2023-12-18 update sinepwm plugin
2023-12-18 renaming plugin joint_unistepper into joint_stepper4pin and adding support for wave/full/half step's (usable for unipolar and l298 driver)
2023-12-19 updating expansion_shiftreg plugin
2023-12-19 updating joint_rcservo plugin
2023-12-21 using extra files for base board configs
2023-12-21 rename the new board key into boardcfg
2023-12-21 removing test-gui generator, please use qt-testgui.py in the main folder, like this: python3 qt-testgui.py configs/TangPrimer20K/config-uart.json 192.168.10.194
2023-12-21 adding config for TangPrimer20K Ext-Lite
2023-12-21 fixing package for TangPrimer20K
2023-12-21 some fixes for rmii 20k
2023-12-21 working minimal config for machxo2
2023-12-22 expand limit on linear axos
2023-12-22 new slot/module configuration
2023-12-22 adding pll generation for MAX 10
2023-12-22 save config to gateware folder
2023-12-22 adding max10 adc support
2023-12-22 reformat
2023-12-22 allow 8/16/32 vins
2023-12-22 adding CH341 (USB2SPI) support to qt-testgui.py to test the SPI interface
2023-12-23 adding FTDI2232H (USB2SPI) support to qt-testgui.py to test the SPI interface
2023-12-23 adding FTDI2232H (USB2SPI) support to rio.c to test the SPI interface - will not work for realtime :(
2023-12-23 adding readme for pif2
2023-12-23 little fixes
2023-12-26 adding corexy setup support
2023-12-27 fixing qtsetup json loading
2023-12-28 moving patch script into files folder
2023-12-28 moving client calculation to plugins (python part)
2023-12-28 spi-testgui: using client calculation from plugins / cleanup interface_w5500.v
2023-12-28 hal-component: using client calculation from plugins
2023-12-29 fixing verilator simulation
2023-12-29 fixing example
2023-12-29 fixing testgui
2024-01-03 fixing loader
2024-01-23 fixing index-encoder function
